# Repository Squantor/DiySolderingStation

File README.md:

# DIY soldering station
This are plans for a DIY (Do it yourself) soldering station. I have currently have a JBC soldering station that I absolutely love but it lacks features, I can shell out the money for a more advanced one but I am also interesting in building one of my own, to my own specifications.
## Requirements
* Supports multiple power outputs
* Supports most JBC hardware like stands, irons, tips
* Supports controllable outputs for turning on air filter pumps when the iron is removed
* Support controllable inputs for turning on soldering tweezer when you are ready to solder
## Directory structure
* [Electronics](electronics/README.md) contains the schematics and PCB's used by the project
* [Firmware](firmware/README.md) contains the software needed for the project, either embedded or PC side software
* [Mechanical](mechanical/README.md) contains drawings of casing/mechanisms etc
## Checking out
This project makes extensive use of submodules, use ```git clone --recurse-submodules https://github.com/Squantor/DiySolderingStation.git``` to clone the repository and its submodules in one go.

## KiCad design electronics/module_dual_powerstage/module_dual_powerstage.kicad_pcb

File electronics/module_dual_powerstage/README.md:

# DiySolder Dual channel power stage
Small module to test out the JBC style power switch. This is used as a patch for existing boards so no respin is needed right away.
## TODO's
Still some things need to be done:
* Review with one night in between
* Produce at [Aisler](https://aisler.net)
* Assemble
* Test & characterise
* update Readme.md with pictures and BOM
## BOM
* Any dual N mosfet in SOIC-8
* Quad optocoupler in DIP
## Pictures
TODO

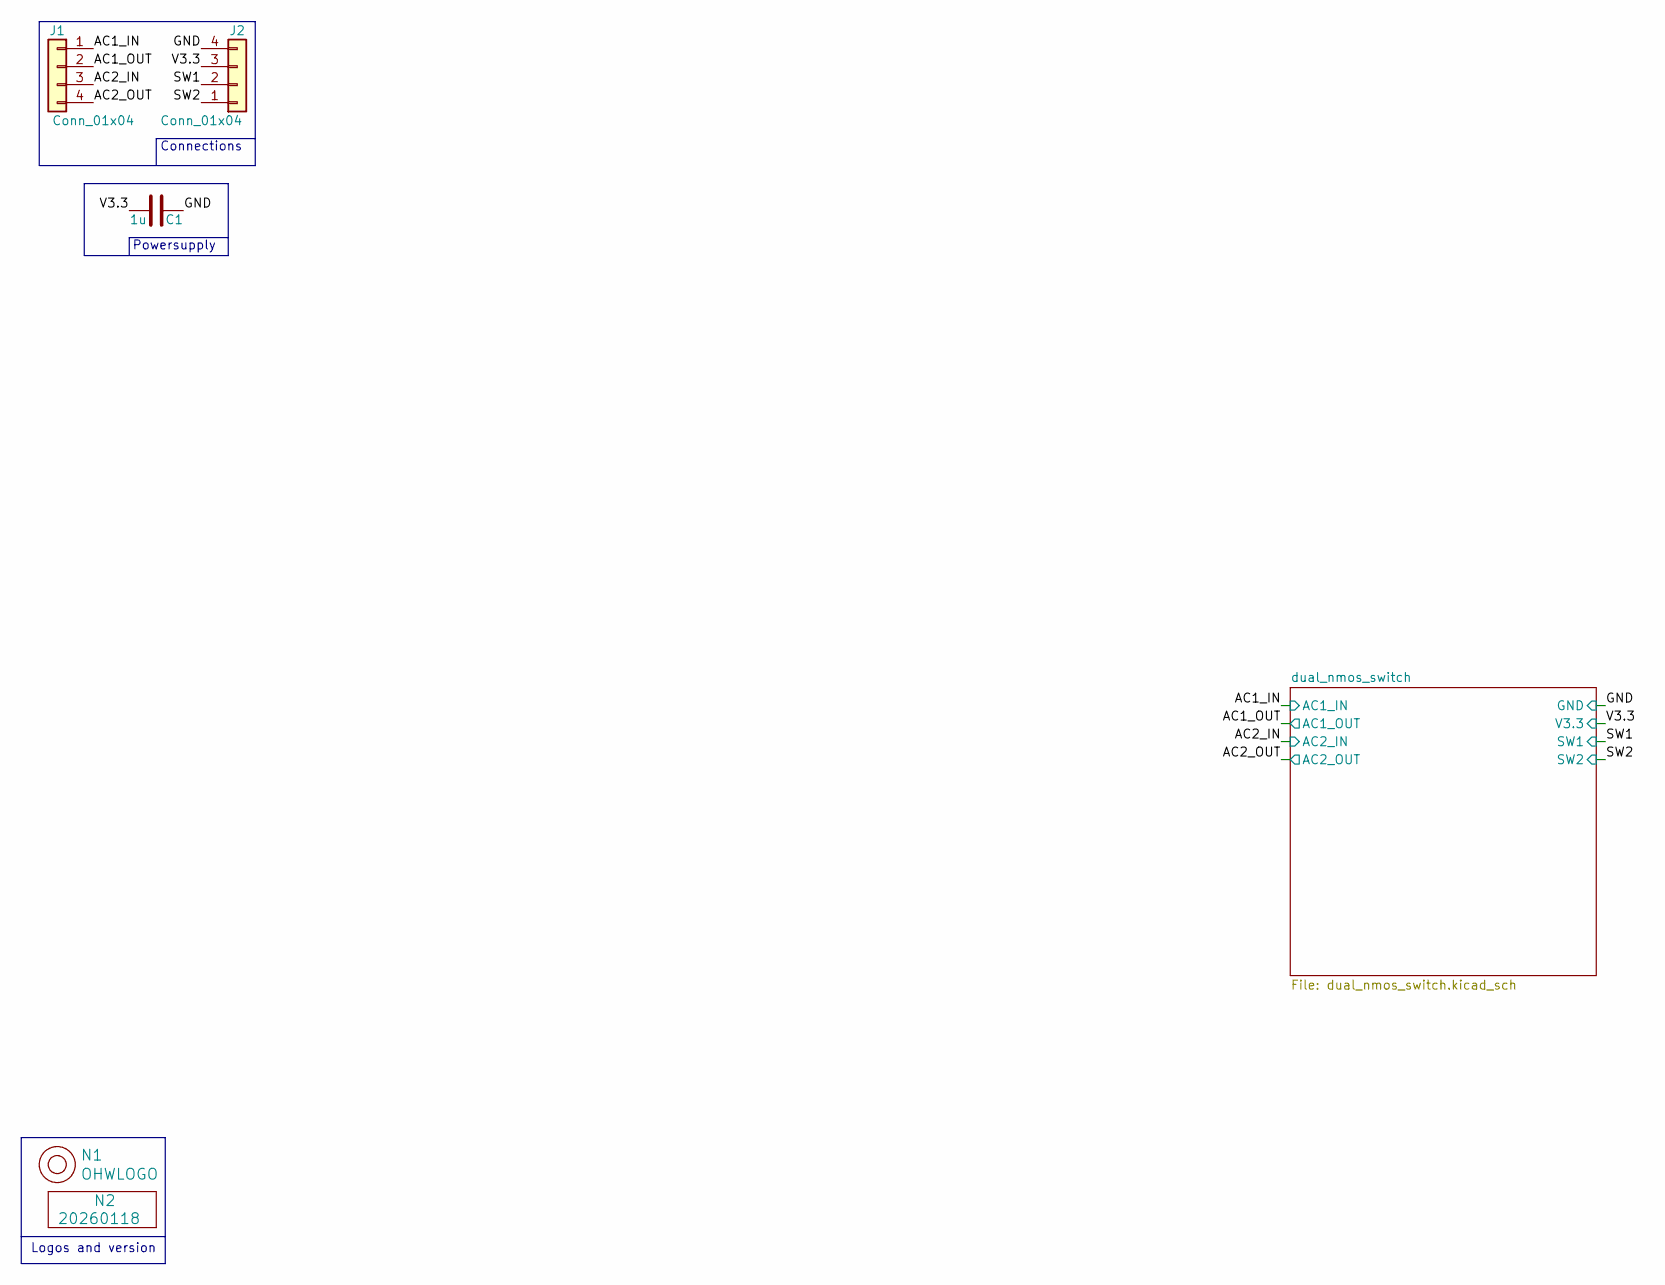
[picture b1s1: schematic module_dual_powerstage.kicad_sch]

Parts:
C1: 1u; C_0805+0603
J1, J2: Conn_01x04; Header-0254-1X04-H010
N1: OHWLOGO; OSHW-Symbol_6.7x6mm_SilkScreen
N2: 20260118; Label_Generic

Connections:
/AC1_IN: J1.1; also elsewhere on the board
/AC1_OUT: J1.2; also elsewhere on the board
/AC2_IN: J1.3; also elsewhere on the board
/AC2_OUT: J1.4; also elsewhere on the board
/GND: C1.2, J2.4; also elsewhere on the board
/SW1: J2.2; also elsewhere on the board
/SW2: J2.1; also elsewhere on the board
/V3.3: C1.1, J2.3; also elsewhere on the board

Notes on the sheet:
Logos and version
Powersupply
Connections

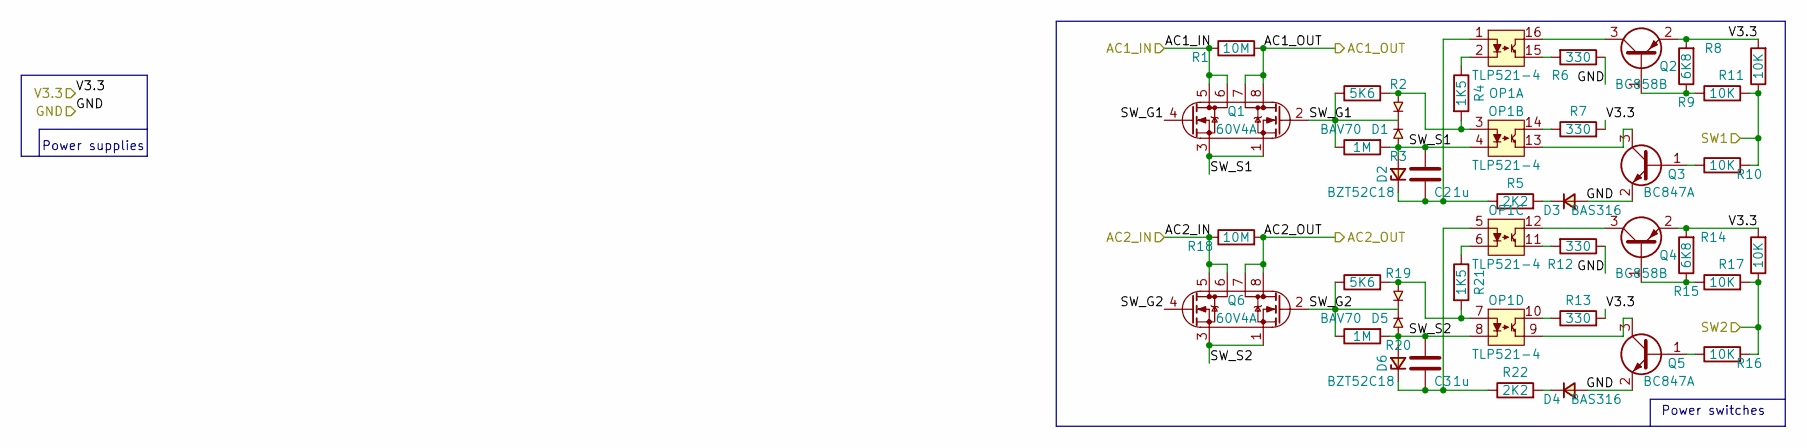
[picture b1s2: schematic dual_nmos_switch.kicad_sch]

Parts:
C2, C3: 1u; C_0805+0603
D1, D5: BAV70; SOT23-3
D2, D6: BZT52C18; SOD-323-nexperia-hand
D3, D4: BAS316; SOD-323-nexperia-hand
OP1: TLP521-4; DIP-16_W7.62mm
Q1, Q6: 60V4A; SOIC-8
Q2, Q4: BC858B; SOT23-3
Q3, Q5: BC847A; SOT23-3
R1, R18: 10M; R_0603_hand
R2, R19: 5K6; R_0603_hand
R3, R20: 1M; R_0603_hand
R4, R21: 1K5; R_0603_hand
R5, R22: 2K2; R_0603_hand
R6, R7, R12, R13: 330; R_0603_hand
R8, R14: 6K8; R_0603_hand
R9, R10, R11, R15, R16, R17: 10K; R_0603_hand

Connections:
/AC1_IN: Q1.5 (D2), Q1.6 (D2), R1.1; also elsewhere on the board
/AC1_OUT: Q1.7 (D1), Q1.8 (D1), R1.2; also elsewhere on the board
/AC2_IN: Q6.5 (D2), Q6.6 (D2), R18.1; also elsewhere on the board
/AC2_OUT: Q6.7 (D1), Q6.8 (D1), R18.2; also elsewhere on the board
/GND: D3.2 (A), D4.2 (A), Q3.2 (E), Q5.2 (E), R6.1, R12.1; also elsewhere on the board
/SW1: R9.2, R10.2, R11.1; also elsewhere on the board
/SW2: R15.2, R16.2, R17.1; also elsewhere on the board
/V3.3: Q2.2 (E), Q4.2 (E), R7.2, R8.2, R11.2, R13.2, R14.2, R17.2; also elsewhere on the board
/dual_nmos_switch/SW_G1: D1.3 (K1A2), Q1.2 (G1), Q1.4 (G2), R2.1, R3.1
/dual_nmos_switch/SW_G2: D5.3 (K1A2), Q6.2 (G1), Q6.4 (G2), R19.1, R20.1
/dual_nmos_switch/SW_S1: C2.2, D1.1 (A1), D2.2 (A), OP1.4 (C2), Q1.1 (S1), Q1.3 (S2), R3.2
/dual_nmos_switch/SW_S2: C3.2, D5.1 (A1), D6.2 (A), OP1.8 (C4), Q6.1 (S1), Q6.3 (S2), R20.2
unnamed: D1.2 (K2), OP1.3 (A2), R2.2, R4.2
unnamed: C2.1, D2.1 (K), OP1.1 (A1), R5.1
unnamed: D3.1 (K), R5.2
unnamed: D4.1 (K), R22.2
unnamed: D5.2 (K2), OP1.7 (A4), R19.2, R21.2
unnamed: C3.1, D6.1 (K), OP1.5 (A3), R22.1
unnamed: OP1.2 (C1), R4.1
unnamed: OP1.15 (E1), R6.2
unnamed: OP1.14 (C2), R7.1
unnamed: OP1.13 (E2), Q3.3 (C)
unnamed: OP1.6 (C3), R21.1
unnamed: OP1.11 (E3), R12.2
unnamed: OP1.10 (C4), R13.1
unnamed: OP1.9 (E4), Q5.3 (C)
unnamed: Q2.1 (B), R8.1, R9.1
unnamed: OP1.16 (C1), Q2.3 (C)
unnamed: Q3.1 (B), R10.1
unnamed: Q4.1 (B), R14.1, R15.1
unnamed: OP1.12 (C3), Q4.3 (C)
unnamed: Q5.1 (B), R16.1

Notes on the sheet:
Power switches
Power supplies

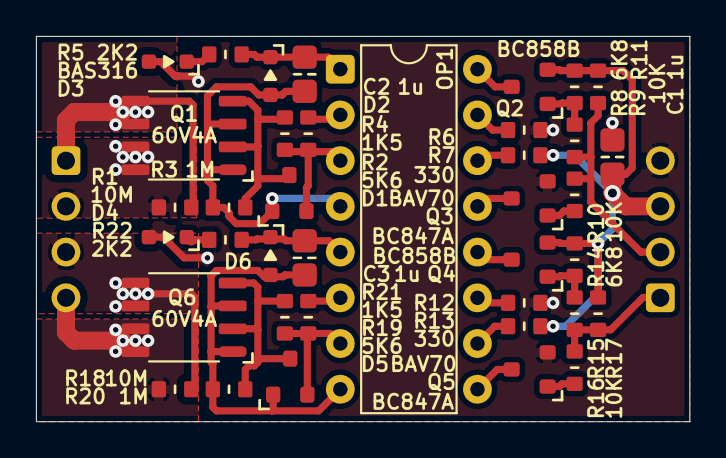
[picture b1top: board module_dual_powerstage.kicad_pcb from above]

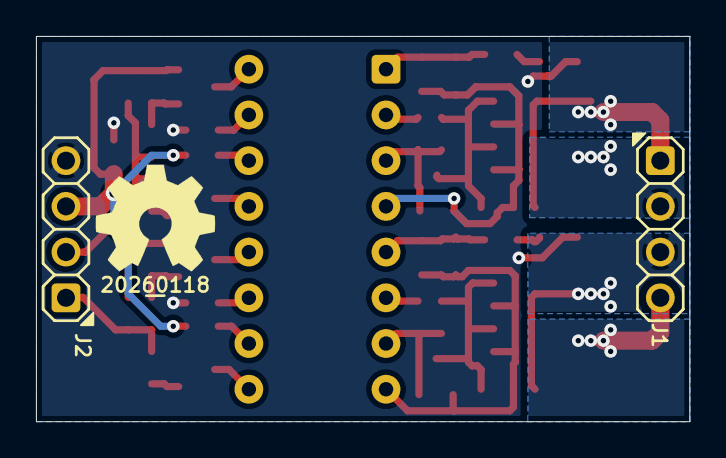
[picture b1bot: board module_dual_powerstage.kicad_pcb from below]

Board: 2 copper layers, 36.3 x 21.4 mm, 42 parts (4 on the bottom side), 32 nets.

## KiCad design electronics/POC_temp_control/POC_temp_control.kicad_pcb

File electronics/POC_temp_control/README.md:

# # Proof of concept JBC T245 and T115 temperature control circuit
Most circuits here are copied/adapted from the [reverse engineered CD-2BC](https://www.eevblog.com/forum/testgear/jbc-soldering-station-cd-2bc-complete-schematic-analysis/) schematic.
# HSI (Hardware Software Interface)
* ADC voltage reference is 3V REF3030AIDBZT
* Crystal connected to pin 0_08 and 0_09
* Pin 0_24: UART RX connected to CH340B TX
* Pin 0_25: UART TX connected to CH340B RX
* Pin 0_12: Bootloader pin connected to switch with 10K pullup and 100nF capacitor, switch impedance is 100Ohm.
## TODO's
Still some things need to be done:
* Review with one night in between
* Produce at [Aisler](https://aisler.net/)
* Assemble
* Test & characterise
* update Readme.md with pictures and BOM
## BOM
TODO
* LM358 SOIC/TSSOP
* OP07 SOIC/TSSOP
* SY8120 DCDC converter
* bunch of zeners
* bunch of NPN/PNP power transistors

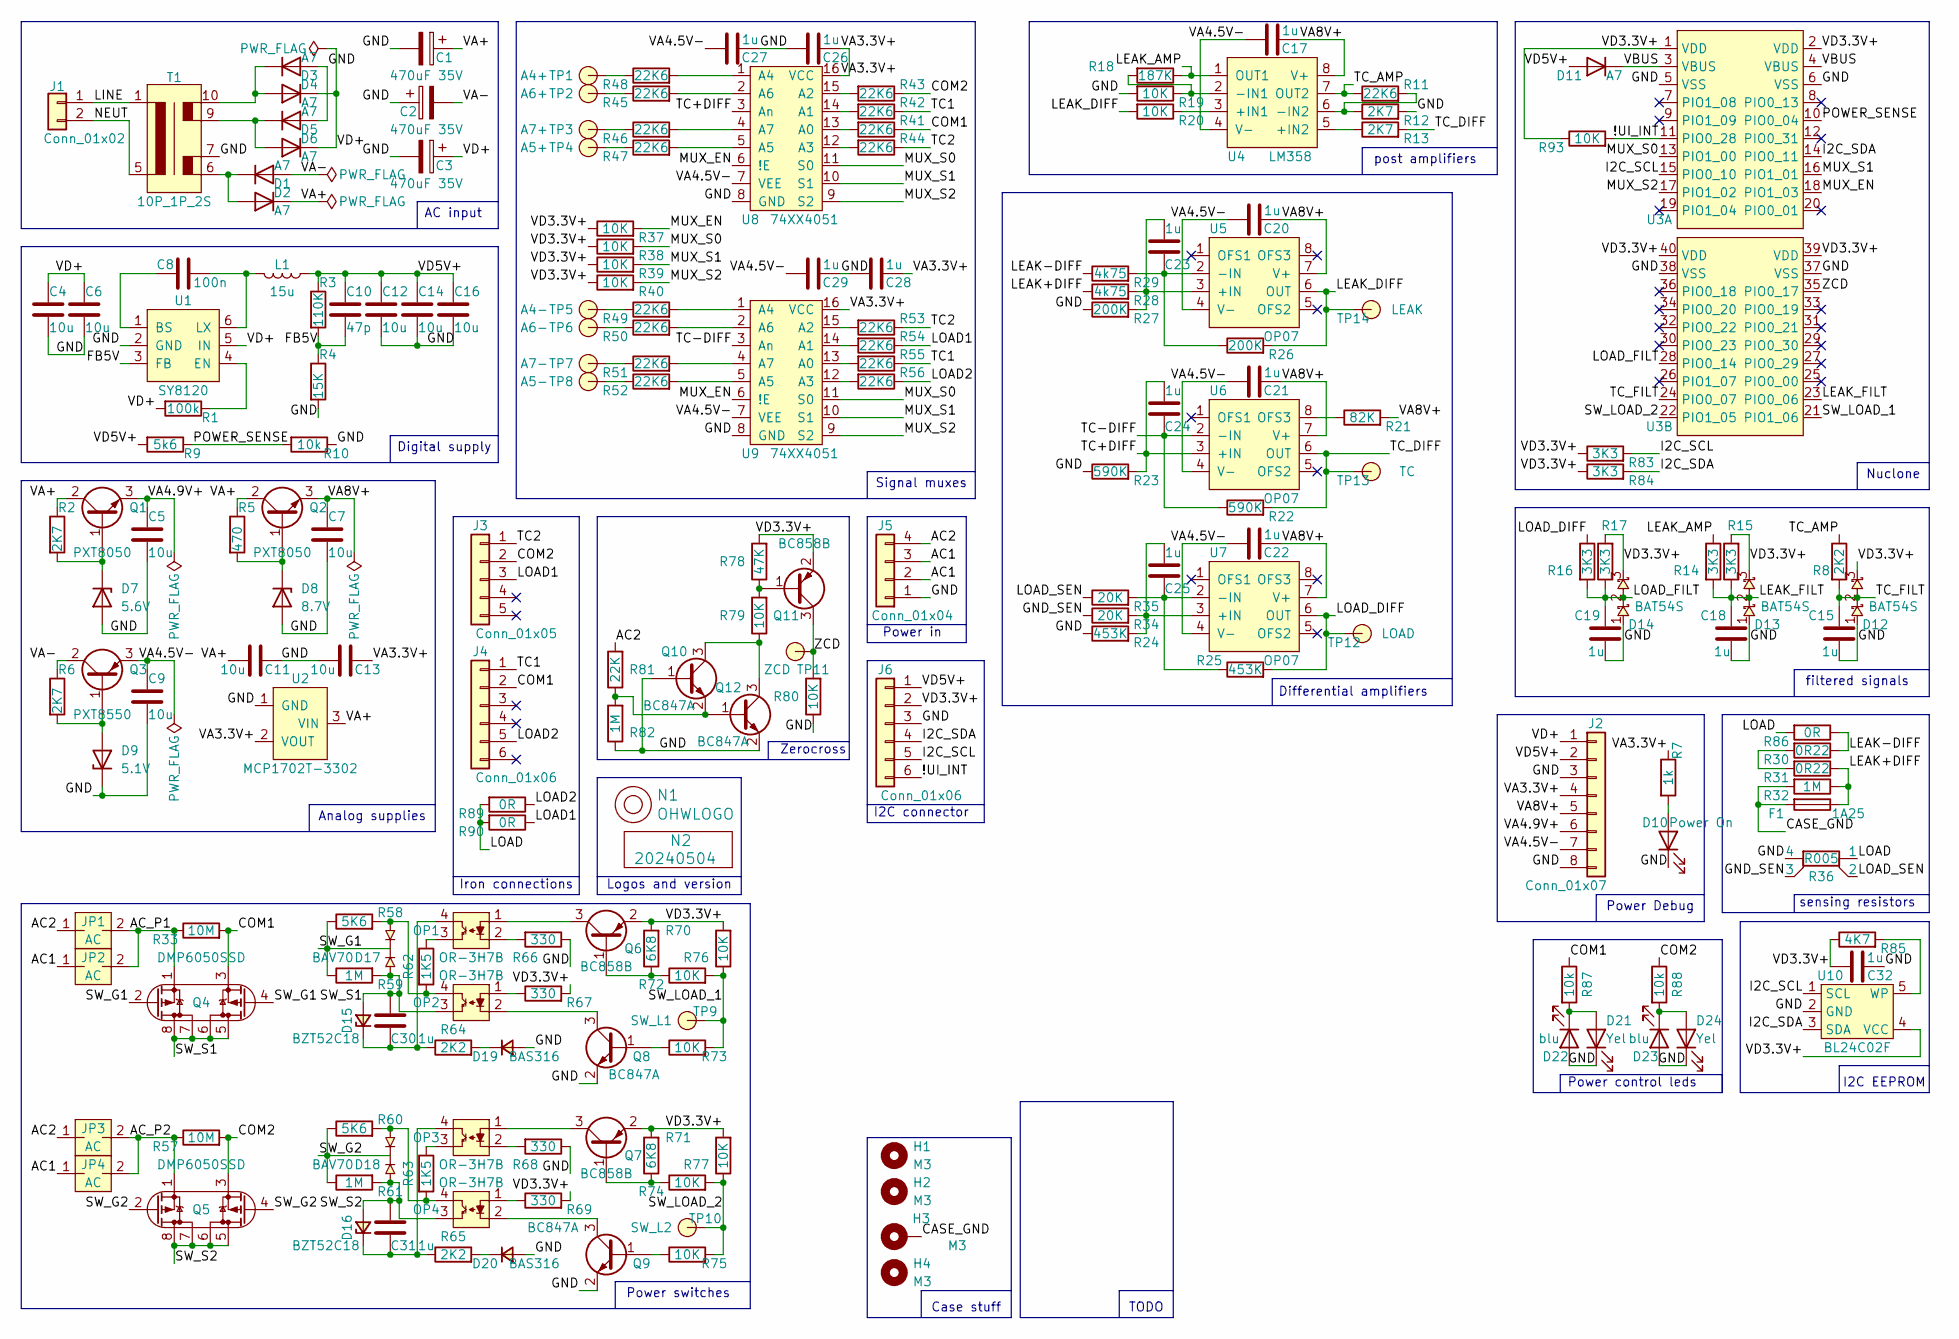
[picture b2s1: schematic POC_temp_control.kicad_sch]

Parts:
C1, C2, C3: 470uF 35V; C-035-080-elco
C4, C6: 10u; C_1206_0805
C5, C7, C9, C11, C12, C13, C14, C16: 10u; C_0805
C8: 100n; C_0603
C10: 47p; C_0603
C15, C17, C18, C19, C20, C21, C22, C30, C31: 1u; C_0805+0603
C23, C24, C25, C26, C27, C28, C29, C32: 1u; C_0603
D1, D2, D3, D4, D5, D6, D11: A7; SOD-123F-hand
D7: 5.6V; SOD-123-hand
D8: 8.7V; SOD-123-hand
D9: 5.1V; SOD-123-hand
D10: Power On; LED_0603_hand
D12, D13, D14: BAT54S; SOT23-3
D15, D16: BZT52C18; SOD-323-nexperia-hand
D17, D18: BAV70; SOT23-3
D19, D20: BAS316; SOD-323-nexperia-hand
D21, D24: Yel; LED_0603_hand
D22, D23: blu; LED_0603_hand
F1: 1A25; FH_XF-155
H1, H2, H3, H4: M3; MountingHole_3.2mm_M3_Pad_Via
J1: Conn_01x02; MKDS_2conn_508pitch_1711725
J2: Conn_01x07; Header-0254-1X08-H008
J3: Conn_01x05; JST_XH_B5B-XH-A_1x05_P2.50mm_Vertical
J4: Conn_01x06; JST_XH_B6B-XH-A_1x06_P2.50mm_Vertical
J5: Conn_01x04; phoenix-MSTBVA-1755752-4p-508-str
J6: Conn_01x06; JST_PH_B6B-PH-K_1x06_P2.00mm_Vertical
JP1, JP2, JP3, JP4: AC; solder_jumper_3mm_SMD
L1: 15u; L_VLS50XXEX_TDK_hand
N1: OHWLOGO; OSHW-Symbol_6.7x6mm_SilkScreen
N2: 20240504; Label_Generic
OP1, OP2, OP3, OP4: OR-3H7B; OP_SOIC_4
Q1, Q2: PXT8050; SOT89-NXP
Q3: PXT8550; SOT89-NXP
Q4, Q5: DMP6050SSD; SOIC-8
Q6, Q7, Q11: BC858B; SOT23-3
Q8, Q9, Q10, Q12: BC847A; SOT23-3
R1: 100k; R_0603_hand
R2, R6, R12, R13: 2K7; R_0603_hand
R3: 110K; R_0603_hand
R4: 15K; R_0603_hand
R5: 470; R_0603_hand
R7: 1k; R_0603_hand
R8, R64, R65: 2K2; R_0603_hand
R9: 5k6; R_0603_hand
R10, R87, R88: 10k; R_0603_hand
R11, R41, R42, R43, R44, R45, R46, R47, R48, R49, R50, R51, R52, R53, R54, R55, R56: 22K6; R_0603_hand
R14, R15, R16, R17, R83, R84: 3K3; R_0603_hand
R18: 187K; R_0603_hand
R19, R20, R37, R38, R39, R40, R72, R73, R74, R75, R76, R77, R79, R80, R93: 10K; R_0603_hand
R21: 82K; R_0603_hand
R22, R23: 590K; R_0603_hand
R24, R25: 453K; R_0603_hand
R26, R27: 200K; R_0603_hand
R28, R29: 4k75; R_0603_hand
R30, R31: 0R22; R_1206
R32: 1M; R_1206
R33, R57: 10M; R_0603_hand
R34, R35: 20K; R_0603_hand
R36: R005; R_1225_kelvin
R58, R60: 5K6; R_0603_hand
R59, R61, R82: 1M; R_0603_hand
R62, R63: 1K5; R_0603_hand
R66, R67, R68, R69: 330; R_0603_hand
R70, R71: 6K8; R_0603_hand
R78: 47K; R_0603_hand
R81: 22K; R_0603_hand
R85: 4K7; R_0603_hand
R86, R89, R90: 0R; R_1206
T1: 10P_1P_2S; 10pin_5pitch_32x27_1Pri_2Sec
TP1: A4+; TestPoint_hole_H03R07
TP2: A6+; TestPoint_hole_H03R07
TP3: A7+; TestPoint_hole_H03R07
TP4: A5+; TestPoint_hole_H03R07
TP5: A4-; TestPoint_hole_H03R07
TP6: A6-; TestPoint_hole_H03R07
TP7: A7-; TestPoint_hole_H03R07
TP8: A5-; TestPoint_hole_H03R07
TP9: SW_L1; TestPoint_hole_H05R10
TP10: SW_L2; TestPoint_hole_H05R10
TP11: ZCD; TestPoint_hole_H05R10
TP12: LOAD; TestPoint_hole_H05R10
TP13: TC; TestPoint_hole_H05R10
TP14: LEAK; TestPoint_hole_H05R10
U1: SY8120; SOT23-6-HAND
U2: MCP1702T-3302; SOT23-3
U3: nuclone_small_LPC845
U4: LM358; SOIC-8
U5, U6, U7: OP07; SOIC-8
U8, U9: 74XX4051; SOIC-16_3.9x9.9mm_P1.27mm
U10: BL24C02F; SOT23-5-Microchip-OT

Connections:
/!UI_INT: J6.6, R93.2, U3.11 (PIO0_28)
/AC1: J5.2, J5.3, JP2.1, JP4.1
/AC2: J5.4, JP1.1, JP3.1, R81.2
/AC_P1: JP1.2, JP2.2, Q4.1 (S1), R33.1
/AC_P2: JP3.2, JP4.2, Q5.1 (S1), R57.1
/CASE_GND: F1.2, H3.1, R32.2
/COM1: J4.2, Q4.3 (S2), R33.2, R41.1, R87.1
/COM2: J3.2, Q5.3 (S2), R43.1, R57.2, R88.1
/FB5V: C10.2, R3.2, R4.1, U1.3 (FB)
/GND: C1.2, C2.1, C3.2, C4.2, C5.2, C6.2, C7.2, C9.2, C11.2, C12.2, C13.1, C14.2, C15.2, C16.2, C18.2, C19.2, C26.1, C27.2, C28.1, C29.2, C32.1, D3.2 (A), D5.2 (A), D7.2 (A), D8.2 (A), D9.1 (K), D10.1 (K), D12.1, D13.1, D14.1, D19.2 (A), D20.2 (A), D21.1 (K), D22.2 (A), D23.2 (A), D24.1 (K), J2.3, J2.8, J5.1, J6.3, Q8.2 (E), Q9.2 (E), Q10.1 (B), Q12.2 (E), R4.2, R10.1, R12.2, R19.2, R23.1, R24.1, R27.1, R36.4, R66.1, R68.1, R80.1, R82.1, T1.7, U1.2 (GND), U2.1 (GND), U3.5 (VSS), U3.6 (VSS), U3.37 (VSS), U3.38 (VSS), U8.8 (GND), U9.8 (GND), U10.2 (GND)
/GND_SEN: R34.1, R36.3
/I2C_SCL: J6.5, R83.2, U3.15 (PIO0_10), U10.1 (SCL)
/I2C_SDA: J6.4, R84.2, U3.14 (PIO0_11), U10.3 (SDA)
/LEAK+DIFF: F1.1, R28.1, R31.1, R32.1
/LEAK-DIFF: R29.1, R30.1, R86.1
/LEAK_AMP: R14.1, R18.1, U4.1 (OUT1)
/LEAK_DIFF: R20.2, R26.2, TP14.1, U5.6 (OUT)
/LEAK_FILT: C18.1, D13.2, R14.2, R15.1, U3.23 (PIO0_06)
/LINE: J1.1, T1.1
/LOAD: R36.1, R86.2, R89.2, R90.2
/LOAD1: J3.3, R54.1, R90.1
/LOAD2: J4.5, R56.1, R89.1
/LOAD_DIFF: R16.1, R25.2, TP12.1, U7.6 (OUT)
/LOAD_FILT: C19.1, D14.2, R16.2, R17.1, U3.28 (PIO0_14)
/LOAD_SEN: R35.1, R36.2
/MUX_EN: R37.2, U3.18 (PIO1_03), U8.6 (!E), U9.6 (!E)
/MUX_S0: R38.2, U3.13 (PIO1_00), U8.11 (S0), U9.11 (S0)
/MUX_S1: R39.2, U3.16 (PIO1_01), U8.10 (S1), U9.10 (S1)
/MUX_S2: R40.2, U3.17 (PIO1_02), U8.9 (S2), U9.9 (S2)
/NEUT: J1.2, T1.5
/POWER_SENSE: R9.1, R10.2, U3.10 (PIO0_04)
/SW_G1: D17.3 (K1A2), Q4.2 (G1), Q4.4 (G2), R58.1, R59.1
/SW_G2: D18.3 (K1A2), Q5.2 (G1), Q5.4 (G2), R60.1, R61.1
/SW_LOAD_1: R72.2, R73.2, R76.1, TP9.1, U3.21 (PIO1_06)
/SW_LOAD_2: R74.2, R75.2, R77.1, TP10.1, U3.22 (PIO1_05)
/SW_S1: C30.2, D15.2 (A), D17.1 (A1), OP2.3, Q4.5 (D2), Q4.6 (D2), Q4.7 (D1), Q4.8 (D1), R59.2
/SW_S2: C31.2, D16.2 (A), D18.1 (A1), OP4.3, Q5.5 (D2), Q5.6 (D2), Q5.7 (D1), Q5.8 (D1), R61.2
/TC1: J4.1, R42.1, R55.1
/TC2: J3.1, R44.1, R53.1
/TC+DIFF: C24.2, R23.2, U6.3 (+IN), U8.3 (An)
/TC-DIFF: C24.1, R22.1, U6.2 (-IN), U9.3 (An)
/TC_AMP: R8.1, R11.1, U4.7 (OUT2)
/TC_DIFF: R13.2, R22.2, TP13.1, U6.6 (OUT)
/TC_FILT: C15.1, D12.2, R8.2, U3.24 (PIO0_07)
/VA3.3V+: C13.2, C26.2, C28.2, J2.4, R7.1, U2.2 (VOUT), U8.16 (VCC), U9.16 (VCC)
/VA4.5V-: C9.1, C17.1, C20.1, C21.1, C22.1, C27.1, C29.1, J2.7, Q3.3 (E), U4.4 (V-), U5.4 (V-), U6.4 (V-), U7.4 (V-), U8.7 (VEE), U9.7 (VEE)
/VA4.9V+: C5.1, J2.6, Q1.3 (E)
/VA8V+: C7.1, C17.2, C20.2, C21.2, C22.2, J2.5, Q2.3 (E), R21.2, U4.8 (V+), U5.7 (V+), U6.7 (V+), U7.7 (V+)
/VA+: C1.1, C11.1, D2.1 (K), Q1.2 (C), Q2.2 (C), R2.1, R5.1, U2.3 (VIN)
/VA-: C2.2, D1.2 (A), Q3.2 (C), R6.1
/VBUS: D11.1 (K), U3.3 (VBUS), U3.4 (VBUS)
/VD3.3V+: C32.2, D12.3, D13.3, D14.3, J6.2, Q6.2 (E), Q7.2 (E), Q11.2 (E), R15.2, R17.2, R37.1, R38.1, R39.1, R40.1, R67.2, R69.2, R70.2, R71.2, R76.2, R77.2, R78.2, R83.1, R84.1, R85.1, R93.1, U3.1 (VDD), U3.2 (VDD), U3.39 (VDD), U3.40 (VDD), U10.4 (VCC)
/VD5V+: C10.1, C12.1, C14.1, C16.1, D11.2 (A), J2.2, J6.1, L1.1, R3.1, R9.2
/VD+: C3.1, C4.1, C6.1, D4.1 (K), D6.1 (K), J2.1, R1.2, U1.5 (IN)
/ZCD: Q11.3 (C), R80.2, TP11.1, U3.35 (PIO0_17)
unnamed: D1.1 (K), D2.2 (A), T1.6
unnamed: D3.1 (K), D4.2 (A), T1.10
unnamed: D5.1 (K), D6.2 (A), T1.9
unnamed: D7.1 (K), Q1.1 (B), R2.2
unnamed: D8.1 (K), Q2.1 (B), R5.2
unnamed: D9.2 (A), Q3.1 (B), R6.2
unnamed: D10.2 (A), R7.2
unnamed: C30.1, D15.1 (K), OP1.4, R64.1
unnamed: C31.1, D16.1 (K), OP3.4, R65.1
unnamed: D17.2 (K2), OP2.4, R58.2, R62.2
unnamed: D18.2 (K2), OP4.4, R60.2, R63.2
unnamed: D19.1 (K), R64.2
unnamed: D20.1 (K), R65.2
unnamed: D21.2 (A), D22.1 (K), R87.2
unnamed: D23.1 (K), D24.2 (A), R88.2
unnamed: OP1.2, R66.2
unnamed: OP1.3, R62.1
unnamed: OP2.1, R67.1
unnamed: OP3.2, R68.2
unnamed: OP3.3, R63.1
unnamed: OP4.1, R69.1
unnamed: Q6.1 (B), R70.1, R72.1
unnamed: OP1.1, Q6.3 (C)
unnamed: Q7.1 (B), R71.1, R74.1
unnamed: OP3.1, Q7.3 (C)
unnamed: Q8.1 (B), R73.1
unnamed: OP2.2, Q8.3 (C)
unnamed: Q9.1 (B), R75.1
unnamed: OP4.2, Q9.3 (C)
unnamed: Q10.3 (C), Q12.3 (C), R79.1
unnamed: Q10.2 (E), Q12.1 (B), R81.1, R82.2
unnamed: Q11.1 (B), R78.1, R79.2
unnamed: R30.2, R31.2
unnamed: R45.1, TP2.1
unnamed: R46.1, TP3.1
unnamed: R47.1, TP4.1
unnamed: R48.1, TP1.1
unnamed: R49.1, TP5.1
unnamed: R50.1, TP6.1
unnamed: R51.1, TP7.1
unnamed: R52.1, TP8.1
unnamed: C8.2, U1.1 (BS)
unnamed: R1.1, U1.4 (EN)
unnamed: C8.1, L1.2, U1.6 (LX)
unnamed: R20.1, U4.3 (+IN1)
unnamed: R13.1, U4.5 (+IN2)
unnamed: R18.2, R19.1, U4.2 (-IN1)
unnamed: R11.2, R12.1, U4.6 (-IN2)
unnamed: C23.2, R27.2, R28.2, U5.3 (+IN)
unnamed: C23.1, R26.1, R29.2, U5.2 (-IN)
unnamed: R21.1, U6.8 (OFS3)
unnamed: C25.2, R24.2, R34.2, U7.3 (+IN)
unnamed: C25.1, R25.1, R35.2, U7.2 (-IN)
unnamed: R41.2, U8.13 (A0)
unnamed: R42.2, U8.14 (A1)
unnamed: R43.2, U8.15 (A2)
unnamed: R44.2, U8.12 (A3)
unnamed: R48.2, U8.1 (A4)
unnamed: R47.2, U8.5 (A5)
unnamed: R45.2, U8.2 (A6)
unnamed: R46.2, U8.4 (A7)
unnamed: R55.2, U9.13 (A0)
unnamed: R54.2, U9.14 (A1)
unnamed: R53.2, U9.15 (A2)
unnamed: R56.2, U9.12 (A3)
unnamed: R49.2, U9.1 (A4)
unnamed: R52.2, U9.5 (A5)
unnamed: R50.2, U9.2 (A6)
unnamed: R51.2, U9.4 (A7)
unnamed: R85.2, U10.5 (WP)

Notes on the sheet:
filtered signals
AC input
Analog supplies
Power switches
Digital supply
Power control leds
Logos and version
I2C EEPROM
Signal muxes
Zerocross
Case stuff
Power in
I2C connector
Differential amplifiers
Iron connections
Power Debug
post amplifiers
TODO
Nuclone
sensing resistors

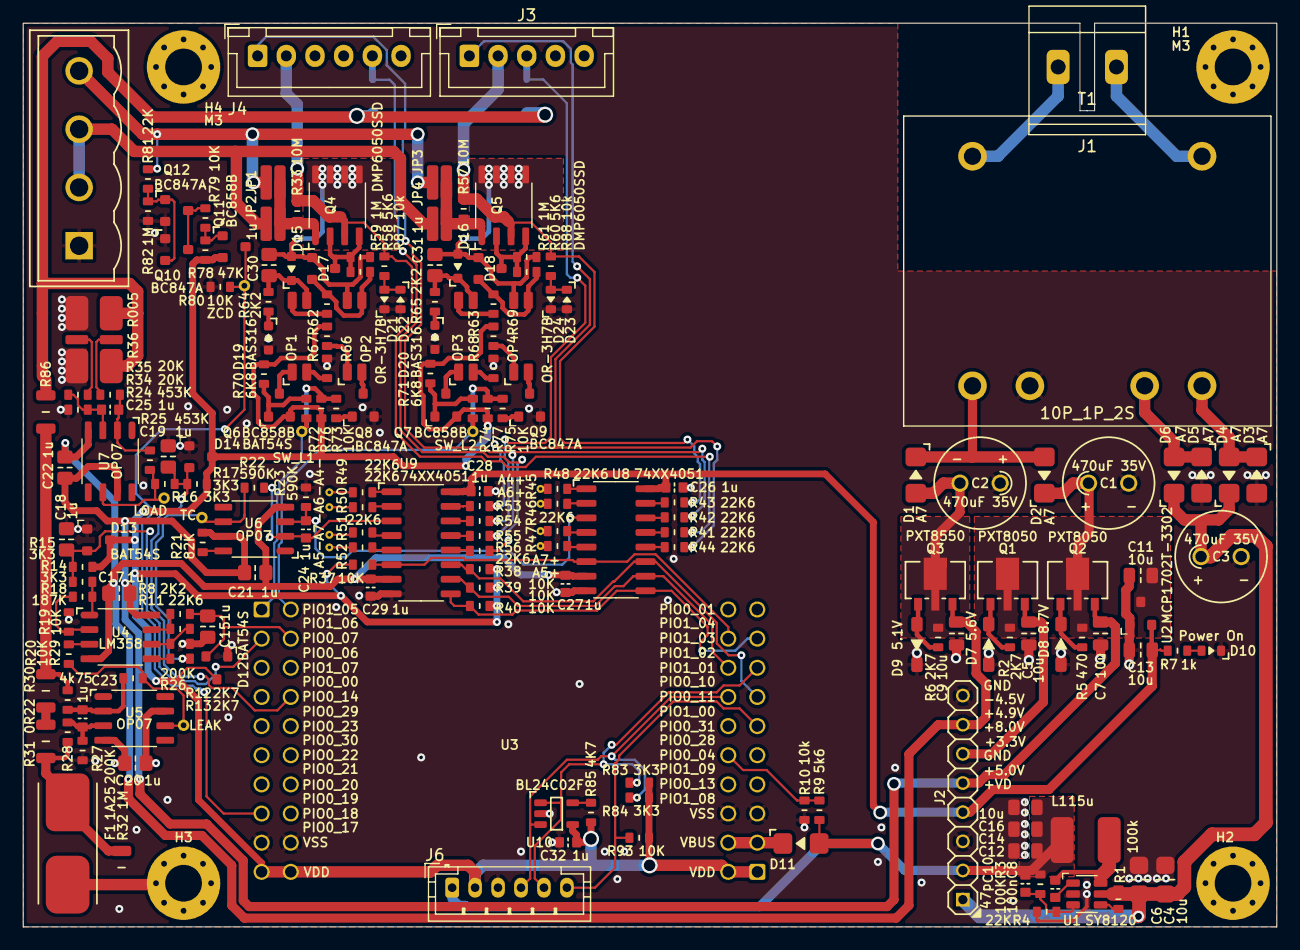
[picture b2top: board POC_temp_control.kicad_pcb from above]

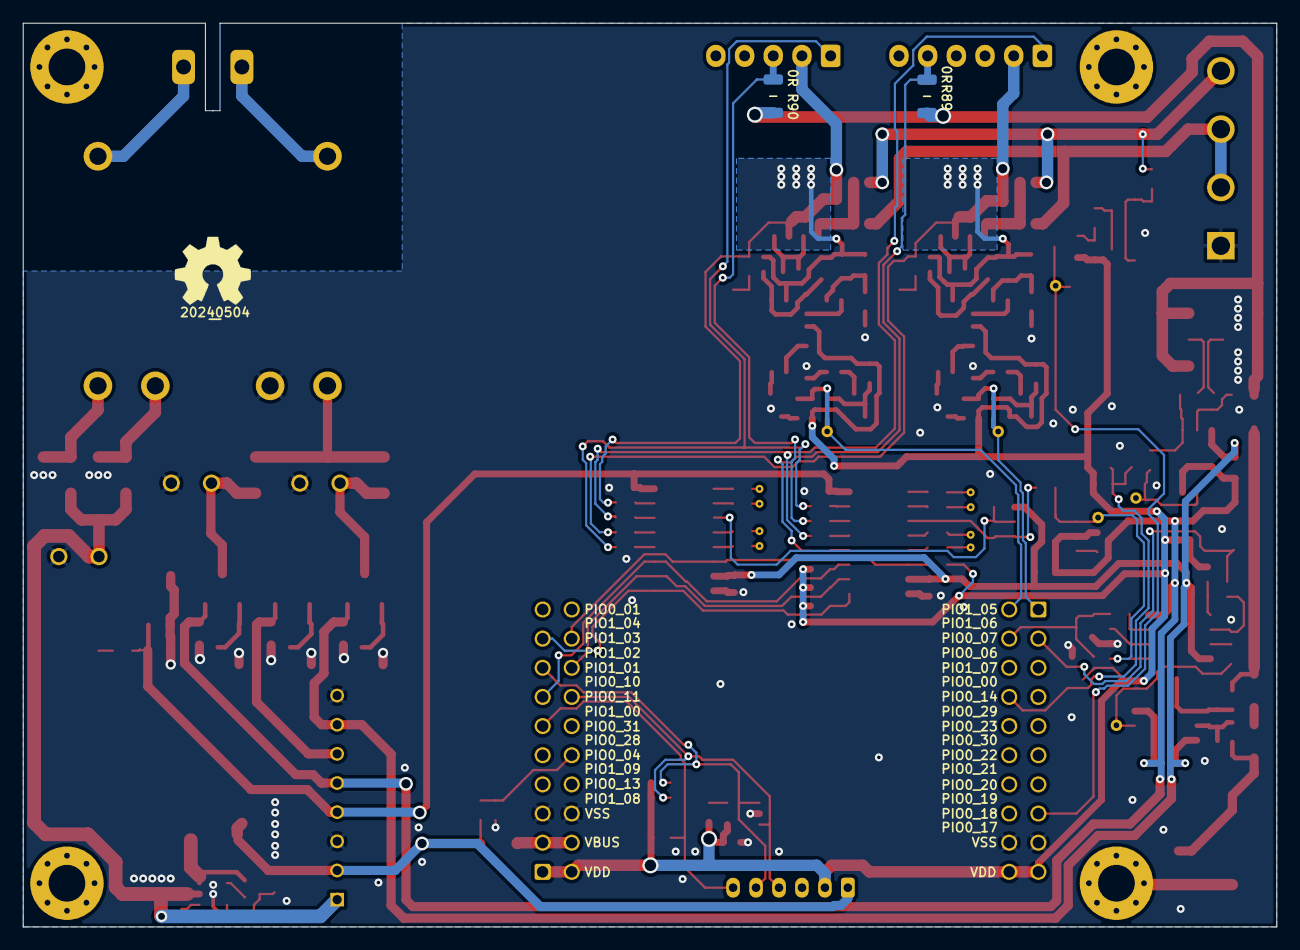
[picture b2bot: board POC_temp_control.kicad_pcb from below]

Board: 2 copper layers, 109.2 x 78.7 mm, 206 parts (4 on the bottom side), 125 nets.

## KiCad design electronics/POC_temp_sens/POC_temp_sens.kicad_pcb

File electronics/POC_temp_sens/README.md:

# Proof of concept JBC T245 and T115 temperature sensing circuit
JBC T245 handle thermocouple sensing circuit as copied/adapted from the [reverse engineered CD-2BC](https://www.eevblog.com/forum/testgear/jbc-soldering-station-cd-2bc-complete-schematic-analysis/) schematic. The PCB is made to imitate a 2.54mm pitch prototyping board cut to size to fit the prototype. On top of this protoboard a small size nuclone with LPC845 microcontroller is put on top.
# HSI (Hardware Software Interface)
* ADC voltage reference is 3V REF3030AIDBZT
* Crystal connected to pin 0_08 and 0_09
* Pin 0_24: UART RX connected to CH340B TX
* Pin 0_25: UART TX connected to CH340B RX
* Pin 0_12: Bootloader pin connected to switch with 10K pullup and 100nF capacitor, switch impedance is 100Ohm.
* Pin 0_04: 5V presence detection done with a resistive divider with 5.6K from 5V to 10K to ground
* Pin 1_00, Pin 1_01, Pin 1_02: 74HC4053 multiplexer 1, pulled down by 100K resistor
  * Mux setting 0: NT115 connector pin 1, C1 connection through 22K 1% resistor
  * Mux setting 1: NT115 connector pin 4, C2 connection through 22K 1% resistor
  * Mux setting 2: NT115 connector pin 3, C3 connection through 22K 1% resistor
  * Mux setting 3: T245 connector pin 1, C1 connection through 22K 1% resistor
  * Mux setting 4: T245 connector pin 5, C2 connection through 22K 1% resistor
  * Mux setting 5: T245 connector pin 2, C3 connection through 22K 1% resistor
  * Mux setting 6:
  * Mux setting 7:
* Pin 1_05, Pin 1_06, Pin 1_07: 74HC4053 multiplexer 2, pulled down by 100K resistor
  * Mux setting 0: NT115 connector pin 5, C1 connection through 22K 1% resistor
  * Mux setting 1: NT115 connector pin 4, C2 connection through 22K 1% resistor
  * Mux setting 2: NT115 connector pin 3, C3 connection through 22K 1% resistor
  * Mux setting 3: T245 connector pin 1, C1 connection through 22K 1% resistor
  * Mux setting 4: T245 connector pin 5, C2 connection through 22K 1% resistor
  * Mux setting 5: T245 connector pin 2, C3 connection through 22K 1% resistor
  * Mux setting 6:
  * Mux setting 7:
* Pin 0_07: Differential voltage with gain X from multiplexer 1 and 2, range X V and filtered by X kohm with X nF
# TODO's
* Building up prototype
* Test & characterise
* update Readme.md with pictures and BOM
# BOM
* OP07 opamp
* LM358 dual opamp
* 74HC4053 multiplexer
* [Small nuclone LPC845](https://github.com/Squantor/squantorDevelBoards/tree/master/electronics/nuclone_LPC845M301BD48_small) with USB2UART and serial flash, 3V ADC voltage reference.
# Pictures
# Measurements

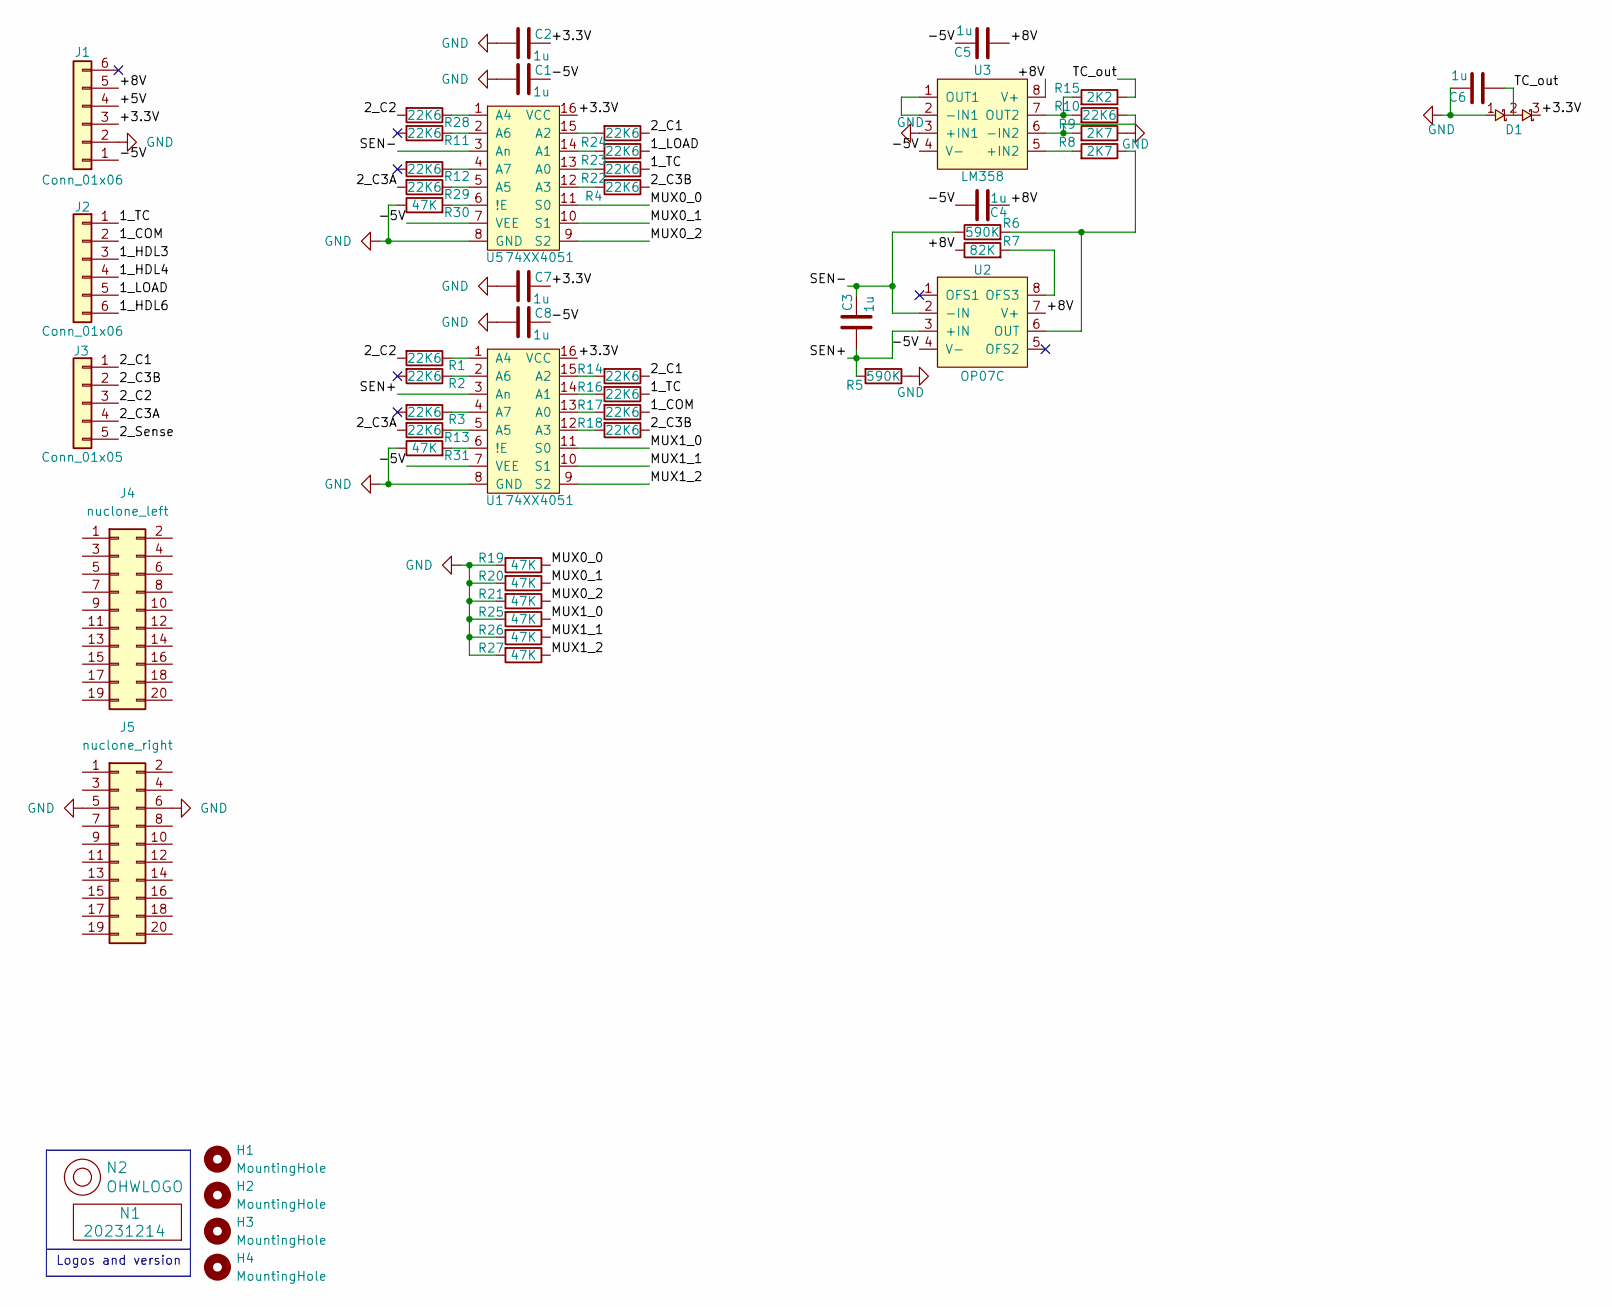
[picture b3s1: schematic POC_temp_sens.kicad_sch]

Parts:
C1, C2, C3, C4, C5, C6, C7, C8: 1u; C_0603
D1: SOT23-3
H1, H2, H3, H4: MountingHole; MountingHole_3.2mm_M3_Pad_Via
J1: Conn_01x06; Molex_KK-254_AE-6410-06A_1x06_P2.54mm_Vertical
J2: Conn_01x06; JST_XH_B6B-XH-A_1x06_P2.50mm_Vertical
J3: Conn_01x05; JST_XH_B5B-XH-A_1x05_P2.50mm_Vertical
J4: nuclone_left; Header-0254-2X10-H010
J5: nuclone_right; Header-0254-2X10-H010
N1: 20231214; Label_Generic
N2: OHWLOGO; OSHW-Symbol_6.7x6mm_SilkScreen
R1, R2, R3, R4, R10, R11, R12, R13, R14, R16, R17, R18, R22, R23, R24, R28, R29: 22K6; R_0603_hand
R5, R6: 590K; R_0603_hand
R7: 82K; R_0603_hand
R8, R9: 2K7; R_0603_hand
R15: 2K2; R_0603_hand
R19, R20, R21, R25, R26, R27, R30, R31: 47K; R_0603_hand
U1, U5: 74XX4051; DIP-16_W7.62mm
U2: OP07C; DIP-8_W7.62mm
U3: LM358; DIP-8_W7.62mm

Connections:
/1_COM: J2.2, R17.1
/1_HDL3: J2.3
/1_HDL4: J2.4
/1_HDL6: J2.6
/1_LOAD: J2.5, R23.1
/1_TC: J2.1, R16.1, R22.1
/2_C1: J3.1, R14.1, R24.1
/2_C2: J3.3, R1.2, R28.2
/2_C3A: J3.4, R13.2, R29.2
/2_C3B: J3.2, R4.1, R18.1
/2_Sense: J3.5
/+3.3V: C2.2, C7.2, D1.3, J1.3, U1.16 (VCC), U5.16 (VCC)
/+5V: J1.4
/+8V: C4.1, C5.1, J1.5, R7.1, U2.7 (V+), U3.8 (V+)
/-5V: C1.2, C4.2, C5.2, C8.2, J1.1, U1.7 (VEE), U2.4 (V-), U3.4 (V-), U5.7 (VEE)
/MUX0_0: R19.1, U5.11 (S0)
/MUX0_1: R20.1, U5.10 (S1)
/MUX0_2: R21.1, U5.9 (S2)
/MUX1_0: R25.1, U1.11 (S0)
/MUX1_1: R26.1, U1.10 (S1)
/MUX1_2: R27.1, U1.9 (S2)
/SEN+: C3.1, R5.2, U1.3 (An), U2.3 (+IN)
/SEN-: C3.2, R6.1, U2.2 (-IN), U5.3 (An)
/TC_out: C6.1, D1.2, R15.1
GND: C1.1, C2.1, C6.2, C7.1, C8.1, D1.1, J1.2, J5.5, J5.6, R5.1, R9.1, R19.2, R20.2, R21.2, R25.2, R26.2, R27.2, R30.1, R31.1, U1.8 (GND), U3.3 (+IN1), U5.8 (GND)
unnamed: R31.2, U1.6 (!E)
unnamed: R17.2, U1.13 (A0)
unnamed: R16.2, U1.14 (A1)
unnamed: R14.2, U1.15 (A2)
unnamed: R18.2, U1.12 (A3)
unnamed: R1.1, U1.1 (A4)
unnamed: R13.1, U1.5 (A5)
unnamed: R2.1, U1.2 (A6)
unnamed: R3.1, U1.4 (A7)
unnamed: R7.2, U2.8 (OFS3)
unnamed: R6.2, R8.1, U2.6 (OUT)
unnamed: R8.2, U3.5 (+IN2)
unnamed: U3.1 (OUT1), U3.2 (-IN1)
unnamed: R9.2, R10.1, U3.6 (-IN2)
unnamed: R10.2, R15.2, U3.7 (OUT2)
unnamed: R30.2, U5.6 (!E)
unnamed: R22.2, U5.13 (A0)
unnamed: R23.2, U5.14 (A1)
unnamed: R24.2, U5.15 (A2)
unnamed: R4.2, U5.12 (A3)
unnamed: R28.1, U5.1 (A4)
unnamed: R29.1, U5.5 (A5)
unnamed: R11.1, U5.2 (A6)
unnamed: R12.1, U5.4 (A7)

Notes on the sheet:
Logos and version
